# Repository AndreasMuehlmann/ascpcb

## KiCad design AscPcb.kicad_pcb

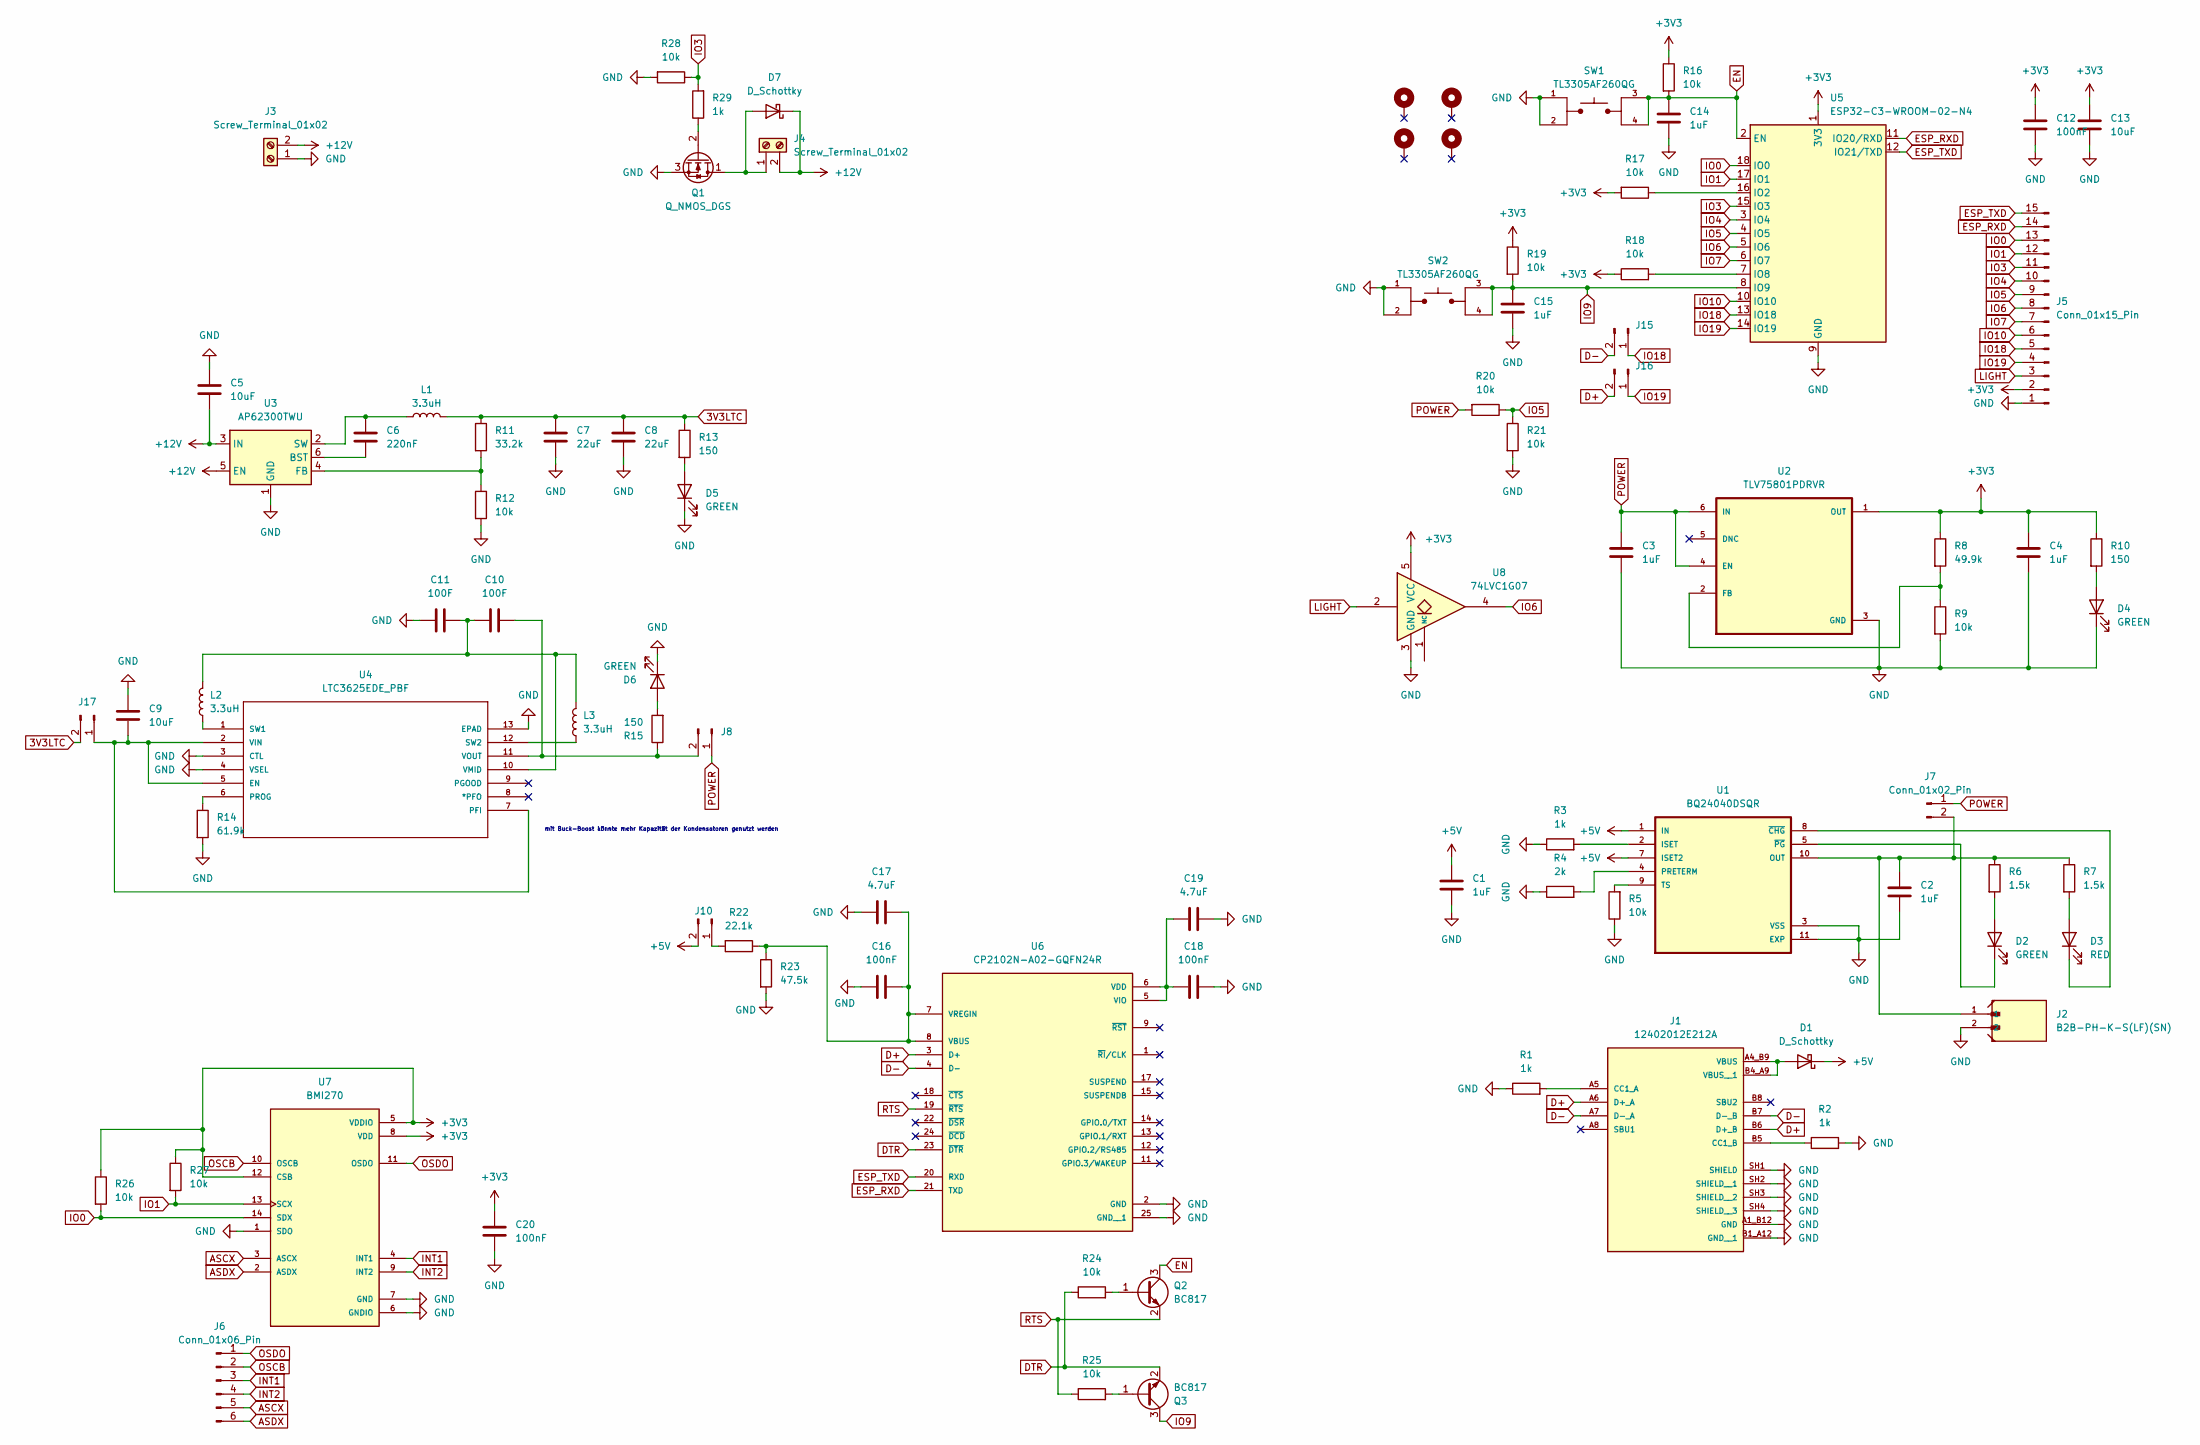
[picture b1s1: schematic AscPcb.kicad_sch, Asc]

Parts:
C1, C2, C3, C4, C14, C15: 1uF; C_0603_1608Metric; MPN CL10B105KP8NNNC
C5: 10uF; C_0603_1608Metric; MPN CL10X106MO8NRNC
C6: 220nF; C_0603_1608Metric; MPN CGA3E3X7R1H224K080AB
C7, C8: 22uF; C_0603_1608Metric; MPN CL10A226MP8NUNE
C9, C13: 10uF; C_0603_1608Metric; MPN CL10A106KQ8NNNC
C10, C11: 100F; CP_Radial_D22.0mm_P10.00mm_SnapIn; MPN TPL-100/22X45F
C12, C16, C18, C20: 100nF; C_0603_1608Metric; MPN C0603C104K8RACTU
C17, C19: 4.7uF; C_0603_1608Metric; MPN CL10A475KP8NNNC
D1, D7: D_Schottky; D_SMA; MPN B240A-13-F
D2, D4, D5, D6: GREEN; LED_0603_1608Metric; MPN 150060GS75000
D3: RED; LED_0603_1608Metric; MPN 150060RS75000
H1, H2, H3, H4: MountingHole_Pad; MountingHole_3.2mm_M3_Pad
J1: 12402012E212A; AMPHENOL_12402012E212A; PARTREV 4
J2: B2B-PH-K-S(LF)(SN); JST_B2B-PH-K-S; MPN B2B-PH-K-S(LF)(SN)
J3, J4: Screw_Terminal_01x02; TerminalBlock_CUI_TB007-508-02_1x02_P5.08mm_Horizontal; MPN TB007-508-02BE
J5: Conn_01x15_Pin; PinHeader_1x15_P2.54mm_Vertical
J6: Conn_01x06_Pin; PinHeader_1x06_P2.54mm_Vertical
J7, J8, J10, J15, J16, J17: Conn_01x02_Pin; PinHeader_1x02_P2.54mm_Vertical
L1, L2, L3: 3.3uH; DR73-3R3-R_EAT; MPN DR73-3R3-R
Q1: Q_NMOS_DGS; SC-59-pads-swapped; MPN DMN1019USN-13
Q2, Q3: BC817; SOT-23; MPN BC817-16LT3G
R1, R2, R3, R29: 1k; R_0603_1608Metric; MPN CRCW06031K00FKEA
R4: 2k; R_0603_1608Metric; MPN RC0603JR-072KL
R5, R9, R12, R16, R17, R18, R19, R20, R21, R24, R25, R26, R27, R28: 10k; R_0603_1608Metric; MPN RC0603FR-0710KL
R6, R7: 1.5k; R_0603_1608Metric; MPN RC0603JR-071K5L
R8: 49.9k; R_0603_1608Metric; MPN TNPW060349K9BEEA
R10, R13, R15: 150; R_0603_1608Metric; MPN CRCW0603150RFKEAC
R11: 33.2k; R_0603_1608Metric; MPN CRCW080533K2FKEA
R14: 61.9k; R_0603_1608Metric; MPN CRCW060361K9FKEA
R22: 22.1k; R_0603_1608Metric; MPN CRCW060322K1FKEA
R23: 47.5k; R_0603_1608Metric; MPN CRCW060347K5FKEAC
SW1, SW2: TL3305AF260QG; SW_TL3305AF260QG; PARTREV C
U1: BQ24040DSQR; SON40P200X200X80-11N; MPN BQ24040DSQR
U2: TLV75801PDRVR; SON65P200X200X80-7N; MPN TLV75801PDRVR
U3: AP62300TWU; TSOT-23-6
U4: LTC3625EDE_PBF; DFN-12_DE; MANUFACTURER_PART_NUMBER ltc3625ede#pbf
U5: ESP32-C3-WROOM-02-N4; ESP32-C3-WROOM-02; MPN ESP32-C3-WROOM-02-N4
U6: CP2102N-A02-GQFN24R; QFN50P400X400X80-25N; PARTREV 1.3
U7: BMI270; XDCR_BMI270
U8: 74LVC1G07; SOT-353_SC-70-5; MPN AIP74LVC1G07GC353.TR; LCSC C4945064

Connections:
3V3LTC: C7.1, C8.1, J17.2, L1.2, R11.1, R13.1
+3V3: C4.1, C12.1, C13.1, C20.1, J5.2, R8.1, R10.1, R16.1, R17.2, R18.1, R19.1, R26.1, R27.1, U2.1 (OUT), U5.1 (3V3), U7.5 (VDDIO), U7.8 (VDD), U7.12 (CSB), U8.5 (VCC)
+5V: C1.2, D1.1 (K), J10.2, U1.1 (IN), U1.7 (ISET2)
+12V: C5.2, D7.1 (K), J3.2, J4.2, U3.3 (IN), U3.5 (EN)
ASCX: J6.5, U7.3 (ASCX)
ASDX: J6.6, U7.2 (ASDX)
D+: J1.A6 (D+_A), J1.B6 (D+_B), J16.2, U6.3 (D+)
D-: J1.A7 (D-_A), J1.B7 (D-_B), J15.2, U6.4 (D-)
DTR: Q3.2 (E), R24.1, U6.23 (~DTR)
EN: C14.1, Q2.3 (C), R16.2, SW1.3, SW1.4, U5.2 (EN)
ESP_RXD: J5.14, U5.11 (IO20/RXD), U6.21 (TXD)
ESP_TXD: J5.15, U5.12 (IO21/TXD), U6.20 (RXD)
GND: C1.1, C2.2, C3.2, C4.2, C5.1, C7.2, C8.2, C9.1, C11.1, C12.2, C13.2, C14.2, C15.2, C16.1, C17.1, C18.1, C19.2, C20.2, D4.1 (K), D5.1 (K), D6.1 (K), J1.A1_B12 (GND), J1.B1_A12 (GND__1), J1.SH1 (SHIELD), J1.SH2 (SHIELD__1), J1.SH3 (SHIELD__2), J1.SH4 (SHIELD__3), J2.2, J3.1, J5.1, Q1.3 (S), R1.1, R2.2, R3.1, R4.1, R5.1, R9.2, R12.2, R14.2, R21.2, R23.2, R28.2, SW1.1, SW1.2, SW2.1, SW2.2, U1.3 (VSS), U1.11 (EXP), U2.3 (GND), U3.1 (GND), U4.3 (CTL), U4.4 (VSEL), U4.13 (EPAD), U5.9 (GND), U5.19 (GND), U6.2 (GND), U6.25 (GND__1), U7.1 (SDO), U7.6 (GNDIO), U7.7 (GND), U8.3 (GND)
INT1: J6.3, U7.4 (INT1)
INT2: J6.4, U7.9 (INT2)
IO0: J5.13, R26.2, U5.18 (IO0), U7.14 (SDX)
IO1: J5.12, R27.2, U5.17 (IO1), U7.13 (SCX)
IO3: J5.11, R28.1, R29.2, U5.15 (IO3)
IO4: J5.10, U5.3 (IO4)
IO5: J5.9, R20.1, R21.1, U5.4 (IO5)
IO6: J5.8, U5.5 (IO6), U8.4
IO7: J5.7, U5.6 (IO7)
IO9: C15.1, Q3.3 (C), R19.2, SW2.3, SW2.4, U5.8 (IO9)
IO10: J5.6, U5.10 (IO10)
IO18: J5.5, J15.1, U5.13 (IO18)
IO19: J5.4, J16.1, U5.14 (IO19)
LIGHT: J5.3, U8.2
unnamed: D1.2 (A), J1.A4_B9 (VBUS), J1.B4_A9 (VBUS__1)
unnamed: D2.2 (A), R6.2
unnamed: D2.1 (K), U1.5 (~PG)
unnamed: D3.2 (A), R7.2
unnamed: D3.1 (K), U1.8 (~CHG)
unnamed: D4.2 (A), R10.2
unnamed: D5.2 (A), R13.2
unnamed: D6.2 (A), R15.2
unnamed: D7.2 (A), J4.1, Q1.1 (D)
unnamed: J1.A5 (CC1_A), R1.2
unnamed: J1.B5 (CC1_B), R2.1
unnamed: C2.1, J2.1, J7.2, R6.1, R7.1, U1.10 (OUT)
unnamed: C10.2, J8.2, R15.1, U4.11 (VOUT)
unnamed: J10.1, R22.2
unnamed: C9.2, J17.1, U4.2 (VIN), U4.5 (EN), U4.7 (PFI)
unnamed: Q1.2 (G), R29.1
unnamed: Q2.1 (B), R24.2
unnamed: Q3.1 (B), R25.2
unnamed: R3.2, U1.2 (ISET)
unnamed: R4.2, U1.4 (PRETERM)
unnamed: R5.2, U1.9 (TS)
unnamed: R8.2, R9.1, U2.2 (FB)
unnamed: C6.2, U3.6 (BST)
unnamed: R11.2, R12.1, U3.4 (FB)
unnamed: C6.1, L1.1, U3.2 (SW)
unnamed: R14.1, U4.6 (PROG)
unnamed: L2.1, U4.1 (SW1)
unnamed: L3.1, U4.12 (SW2)
unnamed: C10.1, C11.2, L2.2, L3.2, U4.10 (VMID)
unnamed: R17.1, U5.16 (IO2)
unnamed: R18.2, U5.7 (IO8)
unnamed: C16.2, C17.2, R22.1, R23.1, U6.7 (VREGIN), U6.8 (VBUS)
unnamed: C18.2, C19.1, U6.5 (VIO), U6.6 (VDD)
OSCB: J6.2, U7.10 (OSCB)
OSDO: J6.1, U7.11 (OSDO)
POWER: C3.1, J7.1, J8.1, R20.2, U2.4 (EN), U2.6 (IN)
RTS: Q2.2 (E), R25.1, U6.19 (~RTS)

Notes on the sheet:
mit Buck-Boost könnte mehr Kapazität der Kondensatoren genutzt werden

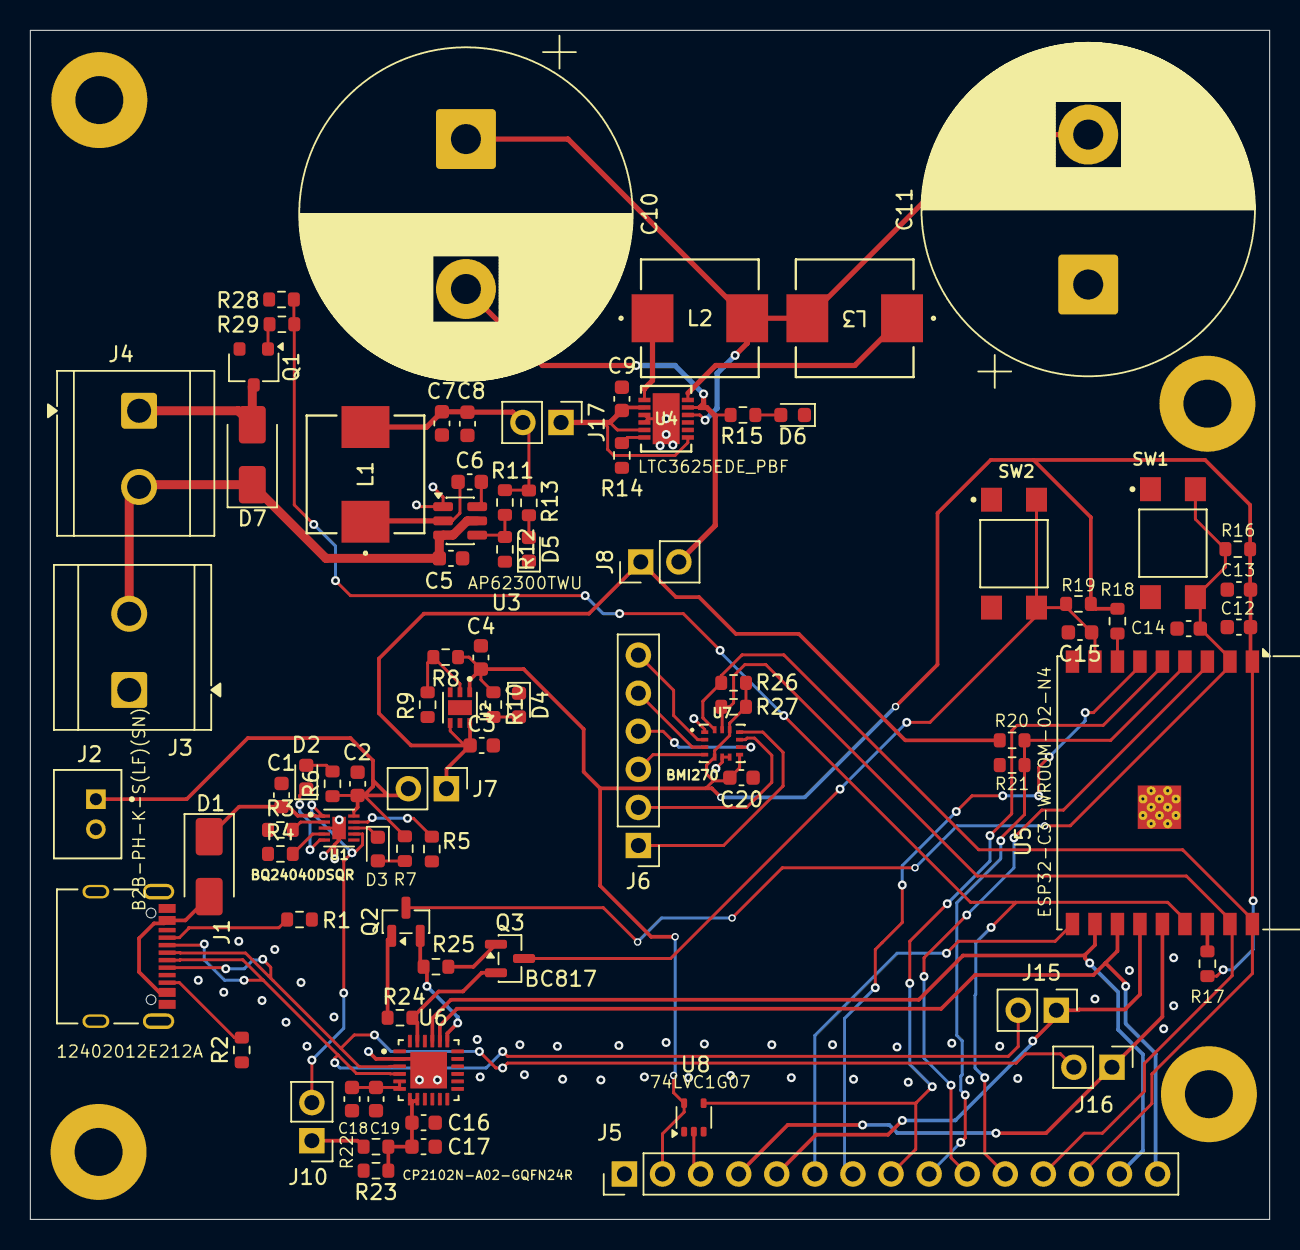
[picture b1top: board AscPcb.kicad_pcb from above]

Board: 2 copper layers, 82.7 x 79.3 mm, 88 parts (0 on the bottom side), 64 nets.

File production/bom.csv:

Designator,Footprint,Quantity,Value,LCSC Part #
"C1, C14, C15, C2, C3, C4",0603,6,1uF,CL10B105KP8NNNC
"C10, C11",CP_Radial_D22.0mm_P10.00mm_SnapIn,2,100F,TPL-100/22X45F
"C12, C16, C18, C20",0603,4,100nF,C0603C104K8RACTU
"C13, C9",0603,2,10uF,CL10A106KQ8NNNC
"C17, C19",0603,2,4.7uF,CL10A475KP8NNNC
C5,0603,1,10uF,CL10X106MO8NRNC
C6,0603,1,220nF,CGA3E3X7R1H224K080AB
"C7, C8",0603,2,22uF,CL10A226MP8NUNE
"D1, D7",D_SMA,2,D_Schottky,B240A-13-F
"D2, D4, D5, D6",0603,4,GREEN,150060GS75000
D3,0603,1,RED,150060RS75000
J1,AMPHENOL_12402012E212A,1,12402012E212A,12402012E212A
"J10, J11, J12, J13, J14, J15, J16, J17, J7, J8",PinHeader_1x02_P2.54mm_Vertical,10,Conn_01x02_Pin,
J2,JST_B2B-PH-K-S,1,B2B-PH-K-S,B2B-PH-K-S(LF)(SN)
"J3, J4",TerminalBlock_CUI_TB007-508-02_1x02_P5.08mm_Horizontal,2,Screw_Terminal_01x02,TB007-508-02BE
J5,PinHeader_1x15_P2.54mm_Vertical,1,Conn_01x15_Pin,
J6,PinHeader_1x06_P2.54mm_Vertical,1,Conn_01x06_Pin,
"L1, L2, L3",DR73-3R3-R_EAT,3,3.3uH,DR73-3R3-R
Q1,SC-59-pads-swapped,1,Q_NMOS_DGS,DMN1019USN-13
"Q2, Q3",SOT-23,2,BC817,BC817-16LT3G
"R1, R2, R29, R3",0603,4,1k,CRCW06031K00FKEA
"R10, R13, R15",0603,3,150,CRCW0603150RFKEAC
R11,0603,1,33.2k,CRCW080533K2FKEA
"R12, R16, R17, R18, R19, R20, R21, R24, R25, R26, R27, R28, R5, R9",0603,14,10k,RC0603FR-0710KL
R14,0603,1,61.9k,CRCW060361K9FKEA
R22,0603,1,22.1k,CRCW060322K1FKEA
R23,0603,1,47.5k,CRCW060347K5FKEAC
R4,0603,1,2k,RC0603JR-072KL
"R6, R7",0603,2,1.5k,RC0603JR-071K5L
R8,0603,1,49.9k,TNPW060349K9BEEA
"SW1, SW2",SW_TL3305AF260QG,2,TL3305AF260QG,TL3305AF260QG
U1,SON40P200X200X80-11N,1,BQ24040DSQR,BQ24040DSQR
U2,SON65P200X200X80-7N,1,TLV75801PDRVR,TLV75801PDRVR
U3,TSOT-23-6,1,AP62300TWU,
U4,DFN-12_DE,1,LTC3625EDE_PBF,
U5,ESP32-C3-WROOM-02,1,ESP32-C3-WROOM-02-N4,ESP32-C3-WROOM-02-N4
U6,QFN50P400X400X80-25N,1,CP2102N-A02-GQFN24R,
U7,XDCR_BMI270,1,BMI270,
U8,SOT-353_SC-70-5,1,74LVC1G07,C4945064

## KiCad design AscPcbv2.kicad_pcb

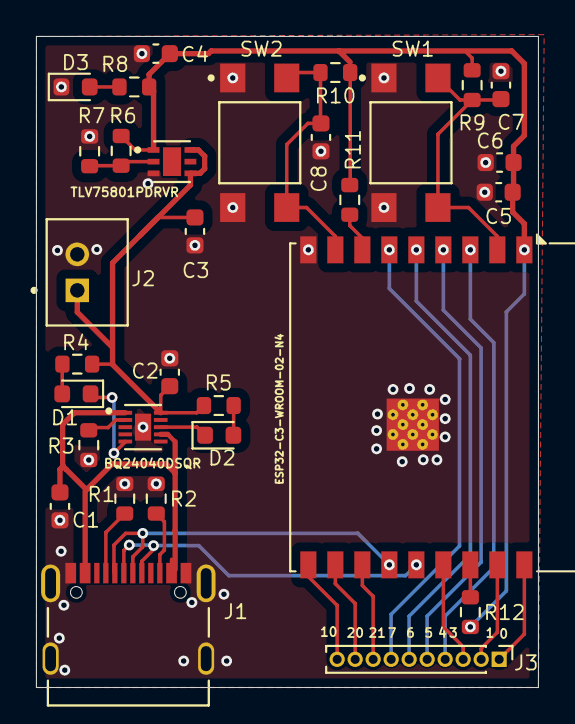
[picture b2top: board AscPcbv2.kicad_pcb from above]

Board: 2 copper layers, 27.9 x 36.2 mm, 31 parts (0 on the bottom side), 29 nets.

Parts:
C1, C2, C3, C4, C7, C8: 1uF; C_0603_1608Metric
C5: 100nF; C_0603_1608Metric
C6: 10uF; C_0603_1608Metric
D1, D3: GREEN; LED_0603_1608Metric
D2: RED; LED_0603_1608Metric
J1: 12402012E212A; AMPHENOL_12402012E212A
J2: B2B-PH-K-S(LF)(SN); JST_B2B-PH-K-S
J3: Conn_01x10_Pin; PinHeader_1x10_P1.00mm_Vertical
R1, R2: 1k; R_0603_1608Metric
R3: 536; R_0603_1608Metric
R4, R5, R8: 150; R_0603_1608Metric
R6, R9, R10, R11, R12: 10k; R_0603_1608Metric
R7: 49.9k; R_0603_1608Metric
SW1, SW2: TL3305AF260QG; SW_TL3305AF260QG
U1: ESP32-C3-WROOM-02-N4; ESP32-C3-WROOM-02
U2: BQ24040DSQR; SON40P200X200X80-11N
U3: TLV75801PDRVR; SON65P200X200X80-7N

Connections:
+3V3: C4.1, C5.1, C6.1, R6.1, R8.1, R9.1, R10.1, R11.1, R12.2, U1.1 (3V3), U3.1 (OUT)
+5V: C1.1, J1.A4_B9 (VBUS), J1.B4_A9 (VBUS__1), U2.1 (IN), U2.7 (ISET2)
D+: J1.A6 (D+_A), J1.B6 (D+_B), U1.14 (IO19)
D-: J1.A7 (D-_A), J1.B7 (D-_B), U1.13 (IO18)
GND: C1.2, C2.2, C3.2, C4.2, C5.2, C6.2, C7.2, C8.2, D3.1 (K), J1.A1_B12 (GND), J1.B1_A12 (GND__1), J1.SH1 (SHIELD), J1.SH2 (SHIELD__1), J1.SH3 (SHIELD__2), J1.SH4 (SHIELD__3), J2.2, R1.1, R2.2, R3.2, R7.2, SW1.1, SW1.2, SW2.1, SW2.2, U1.9 (GND), U1.19 (GND), U2.11 (EXP), U3.3 (GND)
IO0: J3.1, U1.18 (IO0)
IO1: J3.2, U1.17 (IO1)
IO3: J3.3, U1.15 (IO3)
IO4: J3.4, U1.3 (IO4)
IO5: J3.5, U1.4 (IO5)
IO6: J3.6, U1.5 (IO6)
IO7: J3.7, U1.6 (IO7)
IO10: J3.10, U1.10 (IO10)
IO20: J3.9, U1.11 (IO20/RXD)
IO21: J3.8, U1.12 (IO21/TXD)
unnamed: D1.2 (A), R4.2
unnamed: D1.1 (K), U2.5 (~PG)
unnamed: D2.2 (A), R5.2
unnamed: D2.1 (K), U2.8 (~CHG)
unnamed: D3.2 (A), R8.2
unnamed: J1.A5 (CC1_A), R1.2
unnamed: J1.B5 (CC1_B), R2.1
unnamed: C7.1, R9.2, SW1.3, SW1.4, U1.2 (EN)
unnamed: R12.1, U1.16 (IO2)
unnamed: R11.2, U1.7 (IO8)
unnamed: C8.1, R10.2, SW2.3, SW2.4, U1.8 (IO9)
unnamed: R3.1, U2.2 (ISET)
unnamed: R6.2, R7.1, U3.2 (FB)
POWER: C2.1, C3.1, J2.1, R4.1, R5.1, U2.10 (OUT), U3.4 (EN), U3.6 (IN)

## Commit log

2025-09-17 schematic first attempt
2025-09-17 fragen an vrony
2025-09-18 inserted actual capacitors
2025-09-18 MPN and Datasheets for Resistors and generating BOM
2025-09-18 add more actual parts and add datasheets and MPNs
2025-09-18 clean up and other stuff
2025-09-18 LEDs with correct Resistors
2025-09-18 schematic done
2025-09-18 sub circuits put together
2025-09-18 connecting some more stuff
2025-09-19 bad but working version of pcb
2025-09-19 new design: all components placed
2025-09-19 new version of pcb done
2025-09-22 order 1
2025-10-12 added bmi270 and ltc3625 and fixed some errors
2025-10-12 super cap charger fix some errors and basic setup for motor control
2025-10-13 motor control circuit done
2025-10-14 usb to serial converter, some safety features and monitoring
2025-10-18 add schmitt trigger
2025-10-20 bq24 according to datasheet, also fix cp2102, fix naming
2025-10-20 double checked everything in schematic
2025-10-20 started with pcb layout, did usb-c, buck, linear reg, bq24, cp2102
2025-10-21 board layout done but not wired
2025-10-21 first attempt at putting down traces
2025-10-22 routing done not gnd
